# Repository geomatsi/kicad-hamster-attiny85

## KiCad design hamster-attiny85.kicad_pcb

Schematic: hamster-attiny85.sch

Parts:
BT1: BAT; BatteryHolder_Keystone_103_1x20mm
C1: 100uF; CP_Radial_D6.3mm_P2.50mm
C2: 10nF; C_1206_3216Metric_Pad1.42x1.75mm_HandSolder
D1: 1N4148; D_DO-35_SOD27_P7.62mm_Horizontal
R1: 10K; R_1206_3216Metric_Pad1.42x1.75mm_HandSolder
R2: 20K; R_1206_3216Metric_Pad1.42x1.75mm_HandSolder
U1: ATtiny85; SOIJ-8_5.3x5.3mm_P1.27mm
U2: DS18B20; TO-92_Inline
U3: NRF24L01; nRF24L01_Breakout

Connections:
+3V3: BT1.1, C1.1, R1.1, R2.1, U1.8 (VCC), U2.3 (VDD), U3.2
GND: BT1.2, C1.2, C2.2, U1.4 (GND), U2.1 (GND), U3.1
unnamed: C2.1, D1.2, R2.2, U3.4
unnamed: D1.1, U1.7 (PB2), U3.5
unnamed: R1.2, U1.1 (~RESET~/PB5)
unnamed: U1.2 (XTAL1/PB3), U2.2 (DQ)
unnamed: U1.3 (XTAL2/PB4), U3.3
unnamed: U1.5 (AREF/PB0), U3.7
unnamed: U1.6 (PB1), U3.6

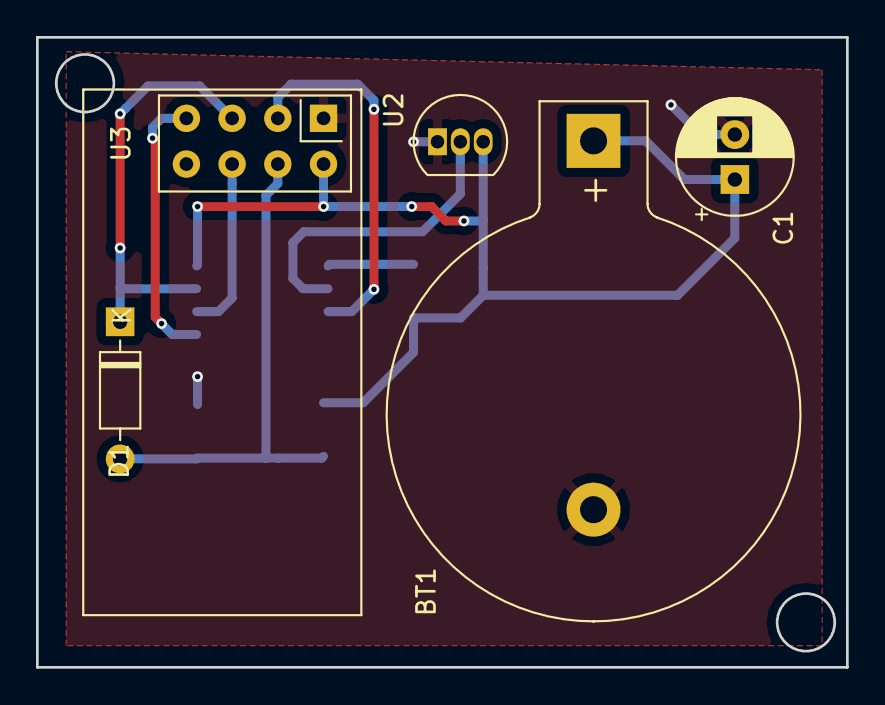
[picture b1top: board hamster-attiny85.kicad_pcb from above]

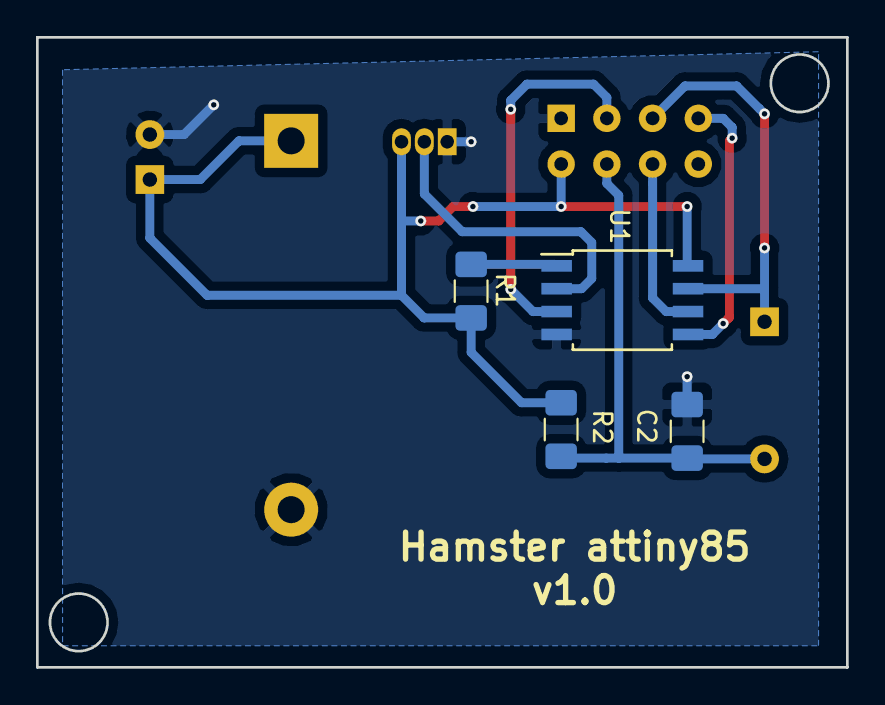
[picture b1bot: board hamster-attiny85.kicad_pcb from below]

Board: 2 copper layers, 45.0 x 35.0 mm, 9 parts (4 on the bottom side), 9 nets.

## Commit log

2018-09-21 hamster-attiny85: kicad4
2018-09-22 hamster-attiny85: kicad5
    Schematics + Layout + Gerbers
2018-09-22 hamster: attiny85: add device 3d view and schematics
